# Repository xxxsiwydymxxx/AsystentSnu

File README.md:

Author: Piotr Szlejter
Project name: Asystent snu, urządzenie mierzące czynniki wpływające na sen
Description:
Urządzenie składa się z 2 części komunikujących się ze sobą bezprzewodowo
urządzenie bazowe posiada czujniki temperatury, ciśnienia atmosferycznego, 
wilgotności powietrza, dodatkowo zawiera czujnik ruchu i mikrofon, dodatkowo
 urządzenie posiada wyświetlacz / możliwość połączenia się z telefonem, 
 dodatkowo urządzenie może posiadać głośnik.
	Urządzenie dodatkowe jest zakładane na nadgarstek/palec i posiada 
pulsometr, oraz czujnik nasycenia krwi tlenem.
	Działanie: urządzenie wykonuje pomiary podczas snu i wyświetla je 
na wyświetlaczu oraz zapisuje do pamięci, dodatkowo urządzenie może 
odtwarzać biały szum przez wbudowany głośnik

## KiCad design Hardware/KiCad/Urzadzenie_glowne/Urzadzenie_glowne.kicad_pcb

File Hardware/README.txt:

Schematy zostały wykonane w programie KiCAD

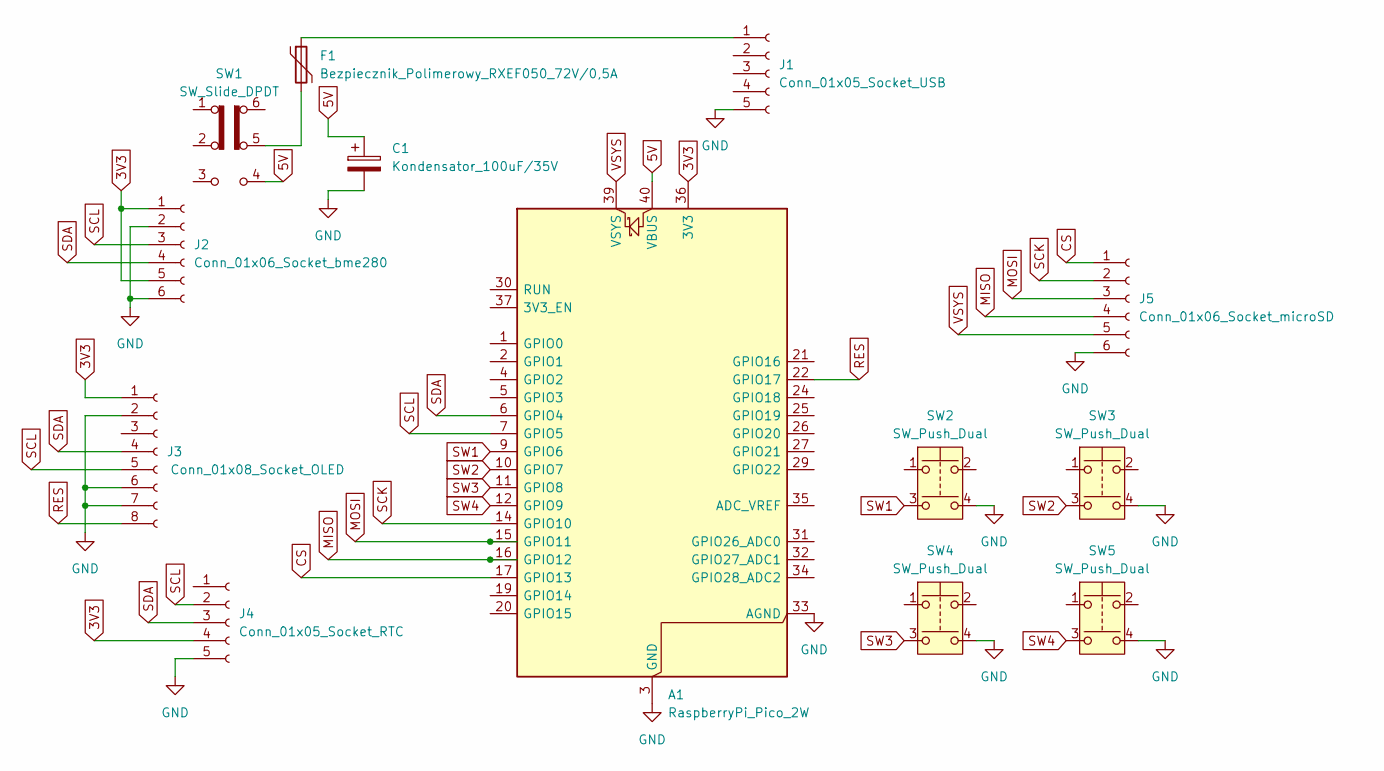
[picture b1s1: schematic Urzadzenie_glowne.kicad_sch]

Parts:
A1: RaspberryPi_Pico_2W; RaspberryPi_Pico_W_SMD_HandSolder
C1: Kondensator_100uF/35V; CP_Radial_D6.3mm_P2.50mm
F1: Bezpiecznik_Polimerowy_RXEF050_72V/0,5A; Fuse_Littelfuse-LVR100
J1: Conn_01x05_Socket_USB; PinSocket_1x05_P2.54mm_Vertical
J2: Conn_01x06_Socket_bme280; PinSocket_1x06_P2.54mm_Vertical
J3: Conn_01x08_Socket_OLED; PinSocket_1x08_P2.54mm_Vertical
J4: Conn_01x05_Socket_RTC; PinSocket_1x05_P2.54mm_Vertical
J5: Conn_01x06_Socket_microSD; PinSocket_1x06_P2.54mm_Vertical
SW1: SW_Slide_DPDT; SW_DPDT_CK_JS202011JCQN
SW2, SW3, SW4, SW5: SW_Push_Dual; SW_DIP_SPSTx02_Slide_6.7x6.64mm_W7.62mm_P2.54mm_LowProfile

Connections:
3V3: A1.36 (3V3), J2.1 (VCC), J2.5 (CSB), J3.1 (VCC), J4.4 (VCC)
5V: A1.40 (VBUS), C1.1, SW1.4 (A)
CS: A1.17 (GPIO13), J5.1 (CS)
GND: A1.3 (GND), A1.8 (GND), A1.13 (GND), A1.18 (GND), A1.23 (GND), A1.28 (GND), A1.33 (AGND), A1.38 (GND), C1.2, J1.5 (GND), J2.2 (GND), J2.6 (SDO), J3.2 (GND), J3.6 (CS), J3.7 (D/C), J4.5 (GND), J5.6 (GND), SW2.4, SW3.4, SW4.4, SW5.4
MISO: A1.16 (GPIO12), J5.4 (MISO)
MOSI: A1.15 (GPIO11), J5.3 (MOSI)
unnamed: F1.2, SW1.5 (B)
unnamed: F1.1, J1.1 (5V)
RES: A1.22 (GPIO17), J3.8 (RES)
SCK: A1.14 (GPIO10), J5.2 (SCK)
SCL: A1.7 (GPIO5), J2.3 (SCL), J3.5 (CLK), J4.2 (SCL)
SDA: A1.6 (GPIO4), J2.4 (SDA), J3.4 (DIN), J4.3 (SDA)
SW1: A1.9 (GPIO6), SW2.3
SW2: A1.10 (GPIO7), SW3.3
SW3: A1.11 (GPIO8), SW4.3
SW4: A1.12 (GPIO9), SW5.3
VSYS: A1.39 (VSYS), J5.5 (VCC)

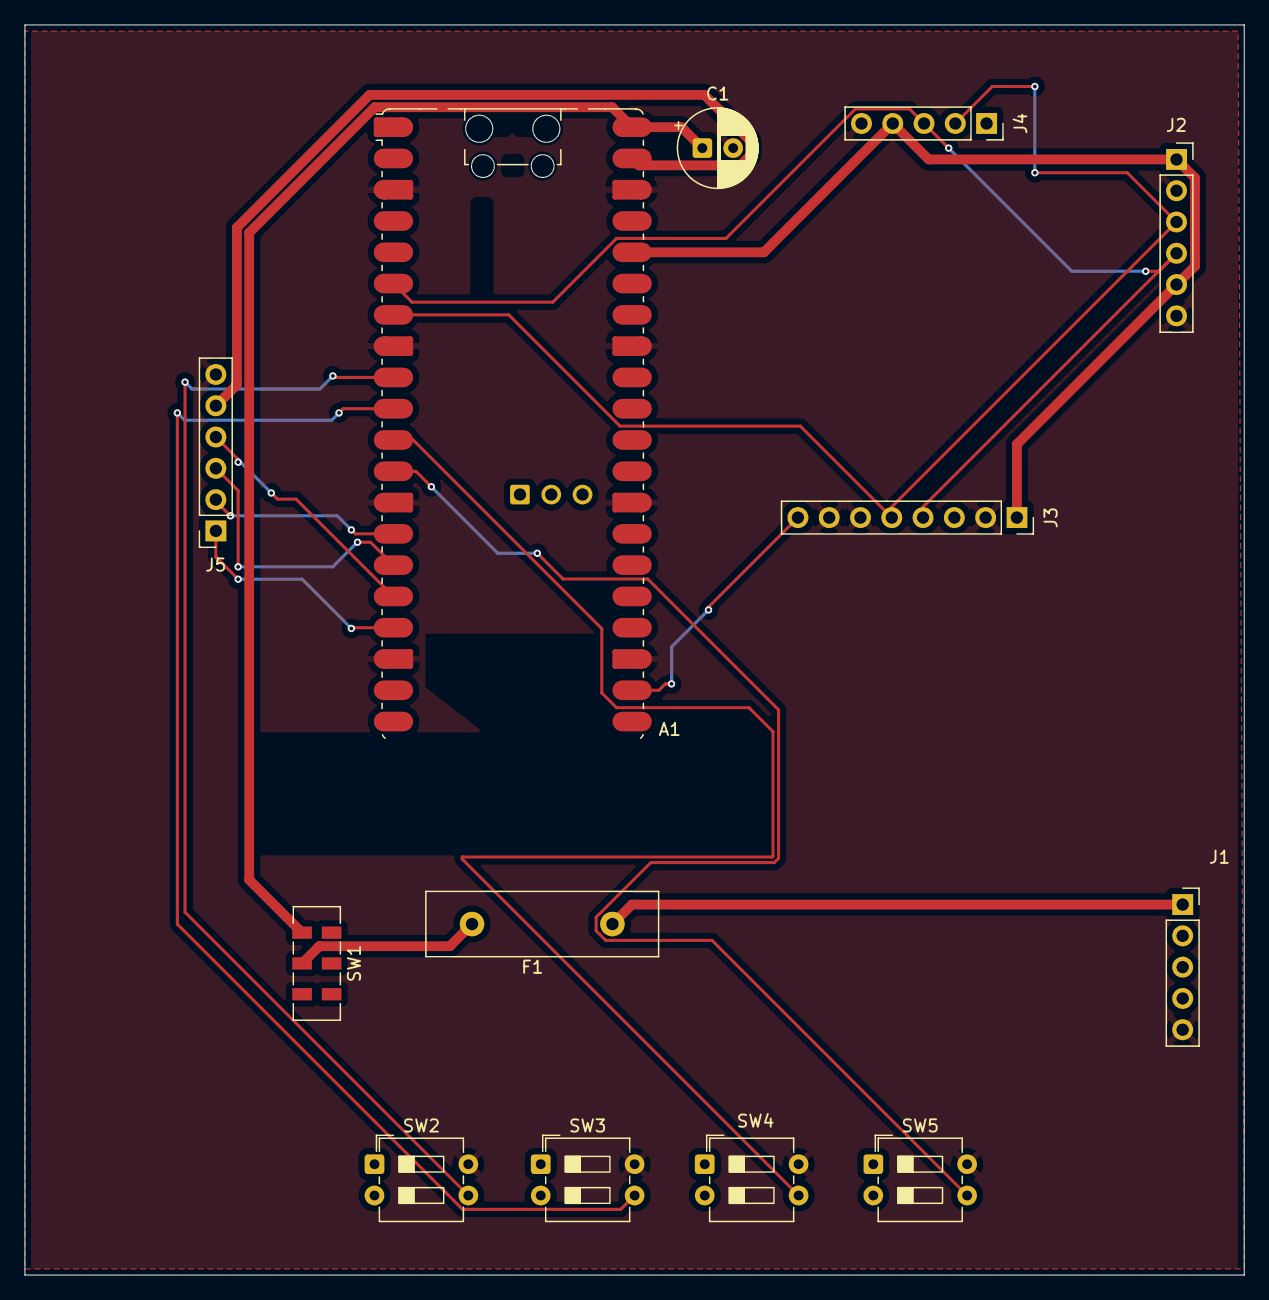
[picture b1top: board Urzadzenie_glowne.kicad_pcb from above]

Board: 2 copper layers, 99.0 x 101.5 mm, 13 parts (0 on the bottom side), 17 nets.

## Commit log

2026-02-16 removed comments
2026-02-19 fixed according to instructions
2026-02-19 added old board pdf
2026-02-20 prezentacja w formacie pdf
